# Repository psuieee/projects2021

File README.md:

# Penn State IEEE
## Projects Committee 2021-2022

### About
This GitHub repository is for the archival and distribution of materials for the Penn State IEEE workshops from Fall 2021 and Spring 2022. Check in releases for files required for workshop attendance.

### Contributing
When contributing to any of the worksohps in this repository, we ask that you make the changes in a fork of the repo and make a pull request to merge into the relevant workshop's branch once the feature is completed. Workshop branches will be merged into *main* only once work on a branch's particular workshop has completed. For more information, please refer to ```./gitproc.md```.
### Credits
| | |
| --- | --- |
| Projects Executive | [Will McGloughlin](https://github.com/wymcg) |
| Projects Committee | [Jackie Cheng](https://github.com/JCheng1100)
| | [Taylor Casavant](https://github.com/tsc061003)
| | [Noah Stansbury](https://github.com/ns-div)
| | [Amal Alsubaie](https://github.com/maldth)
| | [Cole Baughman](https://github.com/ColeBaughman)
| | [Luke Miller](https://github.com/Imperious74)
| Advising | [Ethan Tabler](https://github.com/ethantabler)

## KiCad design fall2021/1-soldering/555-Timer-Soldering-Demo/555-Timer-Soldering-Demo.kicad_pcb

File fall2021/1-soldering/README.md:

# Penn State IEEE
## Soldering Workshop
Thursday, September 2nd from 6-8pm

### About 
A short workshop to teach TH and SMD soldering techniques. In this workshop, participants will learn to solder starting on perfboard, and finishing on a custom 555 demo PCB.

### Required Tools
- Soldering iron and spool of solder
- Hot air rework station (optional)
- Fume extractor (optional)
- Silicon heat pad (optional)

### Parts List
- Demo PCB
- SOIC-8 LM555
- 100nF capacitor
- 220nF capacitor (SMD 1206)
- 1K resistor
- 10K Alps RK09K Potentiometer
- Small Speaker

### Resources
- [Electronics-Tutorials: 555 Generator Circuits](https://www.electronics-tutorials.ws/waveforms/555-circuits-part-1.html)

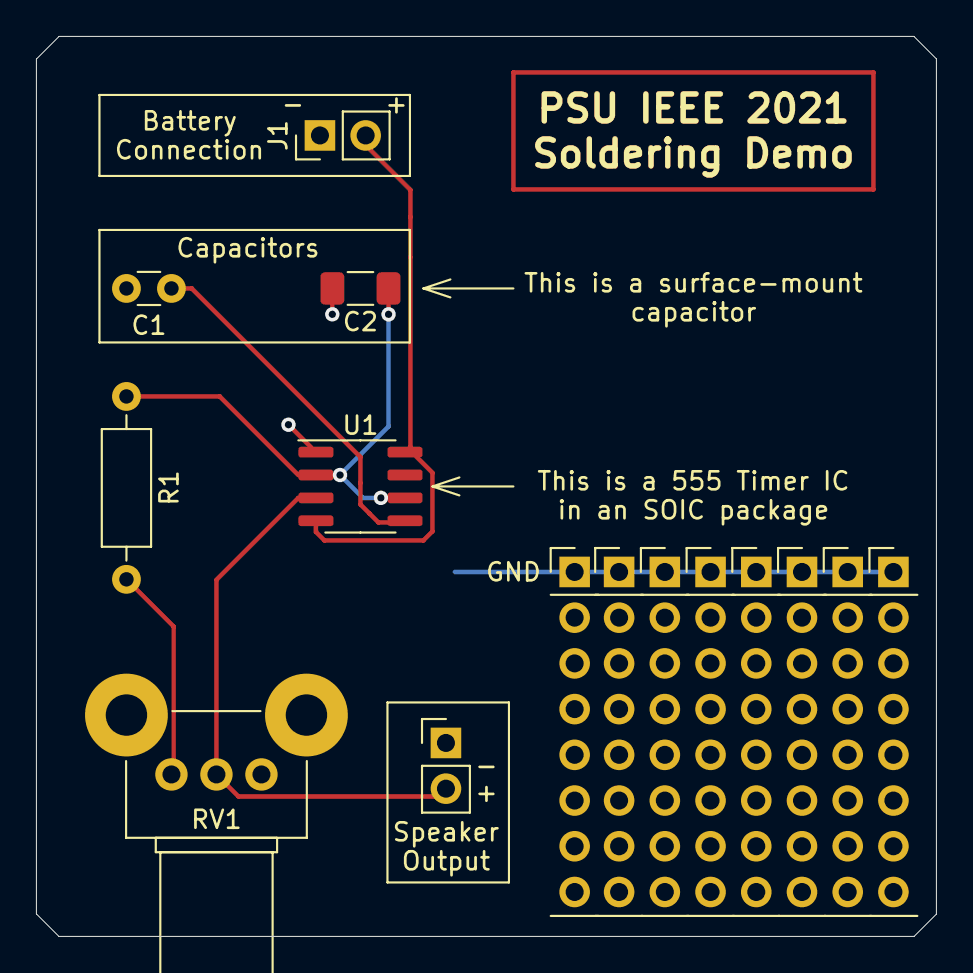
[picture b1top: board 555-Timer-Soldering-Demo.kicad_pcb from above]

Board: 2 copper layers, 50.0 x 50.0 mm, 16 parts (1 on the bottom side), 6 nets.

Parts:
C1: 100nF; C_Disc_D3.0mm_W1.6mm_P2.50mm
C2: 220nF; C_1206_3216Metric_Pad1.33x1.80mm_HandSolder
J1: BatteryTerminal; PinHeader_1x02_P2.54mm_Vertical
J2: Output; PinHeader_1x02_P2.54mm_Vertical
JX1, JX2, JX3, JX4, JX5, JX6, JX7, JX8: Conn_01x07_Male; PinHeader_1x08_P2.54mm
PSU: LOGO; PSU_Logo
R1: 1k; R_Axial_DIN0207_L6.3mm_D2.5mm_P10.16mm_Horizontal
RV1: 10k; Potentiometer_Alps_RK09K_Single_Horizontal
U1: LM555xM; SOIC-8_3.9x4.9mm_P1.27mm

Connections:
/Output: J2.2, RV1.2, U1.3
/VCC: J1.2, U1.4, U1.8
GND: C1.2, C2.2, J1.1, J2.1, JX1.1, JX2.1, JX3.1, JX4.1, JX5.1, JX6.1, JX7.1, JX8.1, U1.1
unnamed: C1.1, U1.5
unnamed: R1.2, RV1.1
Trigger: C2.1, R1.1, U1.2, U1.6

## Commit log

2021-08-16 Initial commit of project files
2021-08-16 changed image folder name in 1-solderingworkshop
2021-08-16 added folders and readmes for the git and gbdev workshops
2021-08-16 Initial Board Design
    On call with Will
2021-08-16 gerber
2021-08-16 Repositioning components & adding text to board
2021-08-17 Added more text & rounded corners
    Updates to README
2021-08-17 Moved working gbdev files onto git
2021-08-17 Rev.A Final
2021-08-20 Update README.md
    Still need date, will add later
2021-08-20 Deleted VBA config
2021-08-20 Update README.md
    Missing date, will add later.
2021-08-21 Clarifying change in 3-gbdev readme
2021-08-21 Added global gitignore
2021-08-21 Added 3-gbdev .gb files to gitignore
2021-08-21 Added makefile clarification in 3-gbdev readme
2021-08-22 Updated Image in README
2021-08-23 Wrote outline for 2-git presentation
2021-08-23 added starting outline for 3-gbdev presentation
2021-08-24 Changed filename of workshopDescriptionTemplate
2021-08-26 Added Jackie
2021-08-31 added contribution statement in main readme
2021-08-31 Removed misleading sentence in contribution statement
2021-09-01 Pre-Final README Updates
    Date of workshop; png of circuit schematic
2021-09-01 Added gitproc.md
2021-09-01 Added reference to pr
2021-09-01 Added slides
2021-09-14 added CHANGEME.txt for workshop
2021-09-14 Made a change to CHANGEME.txt
2021-09-16 Entered my one line... PG-13, of course.
2021-09-16 Test Commit
2021-09-16 I've made a change to CHANGEME.txt
2021-09-16 Made a change to CHANGE.txt
2021-09-17 Added workshop slides
2021-09-17 Added Committee members to main readme
2021-09-17 Moved Ethan on main readme
2021-09-19 Added empty template README for 4-rfid
2021-09-19 added existing debugger code
2021-09-19 added .vscode to .gitignore
2021-09-19 comments
2021-09-20 Minor Changes
2021-09-21 Changed default serial baudrate for optional bluetooth module
2021-09-26 confinedsprite
    Added confinedsprite as an extension to movesprite
2021-09-26 Updated confinedsprite
    Made changes as requested.
    1.Changed outfile name to ConfinedSprite.gb
    2.Deleted old MoveSprite.gb
    3.Added new outfile to .gitignore text file
2021-09-27 Added sample sprites
2021-10-06 added read and write examples
2021-10-13 added skeleton code for read and write examples
2021-10-14 changed .ino filenames for skeleton code
2021-10-14 removed more code from skeleton
2021-10-17 Presentation slides upload and README edit
2022-01-31 Create 7-Rubduck
2022-01-31 Create blank
2022-02-02 Added Linux workshop files
2022-09-15 Microcontrollers Workshop ESP32 Webserver sketch
2022-09-15 Create fall2022
2022-09-15 Create R-Pi Pico Code
